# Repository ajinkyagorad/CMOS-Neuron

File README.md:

# Neuromorphic-CMOS
CMOS neuron based electronics

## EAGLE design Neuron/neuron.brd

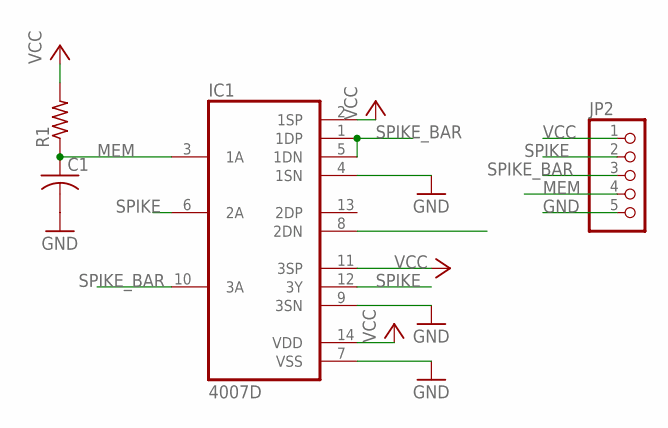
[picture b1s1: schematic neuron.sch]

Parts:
C1: C-USC0805; C0805
IC1: 4007D; SO14
JP2: PINHD-1X5; 1X05
R1: R-US_R0805; R0805

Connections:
GND: C1.2, IC1.4 (1SN), IC1.7 (VSS), IC1.9 (3SN), JP2.5
MEM: C1.1, IC1.3 (1A), IC1.8 (2DN), JP2.4, R1.1
SPIKE: IC1.6 (2A), IC1.12 (3Y), JP2.2
SPIKE_BAR: IC1.1 (1DP), IC1.5 (1DN), IC1.10 (3A), JP2.3
VCC: IC1.2 (1SP), IC1.11 (3SP), IC1.14 (VDD), JP2.1, R1.2

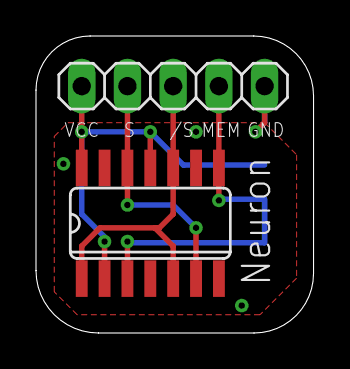
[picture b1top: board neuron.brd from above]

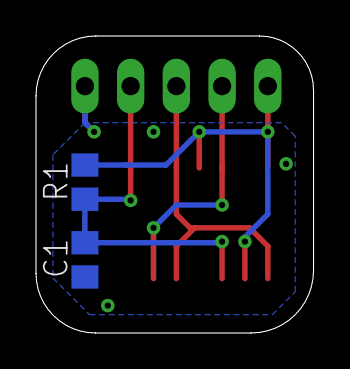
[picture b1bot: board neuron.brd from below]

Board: 2 copper layers, 15.4 x 16.5 mm, 4 parts (2 on the bottom side), 5 nets.

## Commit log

2019-04-17 CD4007 Neuron design
2019-04-17 PCB image
